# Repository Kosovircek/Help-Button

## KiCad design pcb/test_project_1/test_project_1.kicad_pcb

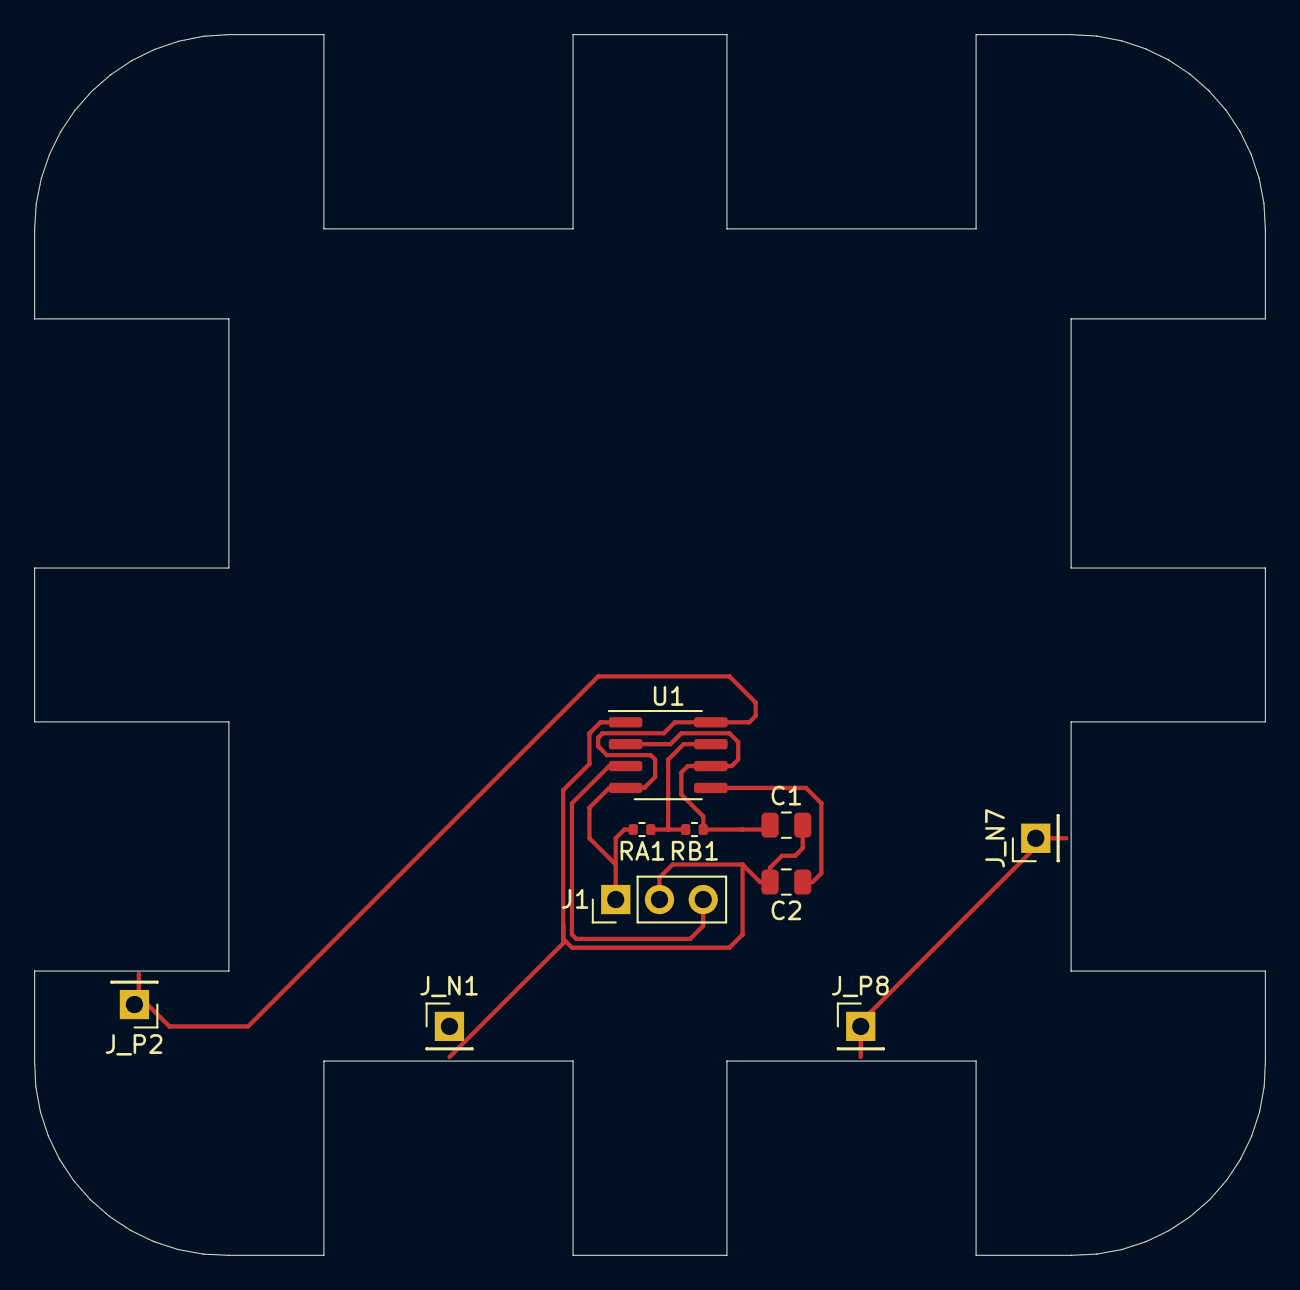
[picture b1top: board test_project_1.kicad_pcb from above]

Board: 2 copper layers, 71.5 x 70.9 mm, 10 parts (0 on the bottom side), 7 nets.

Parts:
C1: 1uF; C_0805_2012Metric
C2: 10nF; C_0805_2012Metric
J1: Conn_01x03_Female; PinHeader_1x03_P2.54mm_Vertical
J_N1, J_N7: Conn_01x01_Male; PinHeader_1x01_P2.54mm_Vertical
J_P2, J_P8: Conn_01x01_Male; PinHeader_1x01_P2.54mm_Vertical
RA1: 1k; R_0402_1005Metric
RB1: 100k; R_0402_1005Metric
U1: LM555CM; SOIC-8_3.9x4.9mm_P1.27mm

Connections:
+12V: J1.1, J_P2.1, RA1.1, U1.4 (R), U1.8 (VCC)
GND: C1.2, C2.2, J1.2, J_N1.1, U1.1 (GND)
unnamed: C1.1, RB1.2, U1.2 (TR), U1.6 (THR)
unnamed: C2.1, U1.5 (CV)
unnamed: J1.3, U1.3 (Q)
unnamed: J_N7.1, J_P8.1
unnamed: RA1.2, RB1.1, U1.7 (DIS)

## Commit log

2024-06-18 first
